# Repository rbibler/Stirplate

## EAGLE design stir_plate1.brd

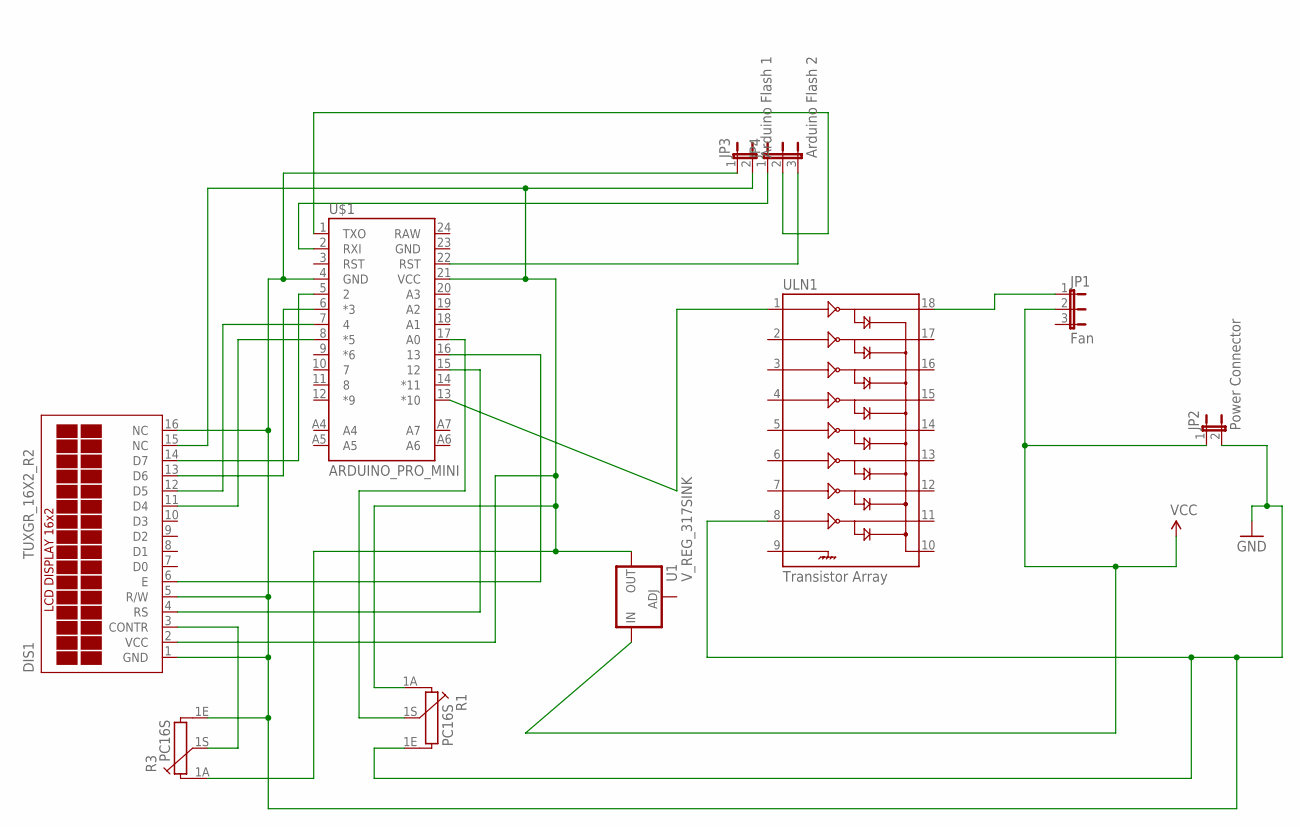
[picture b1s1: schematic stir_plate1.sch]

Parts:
DIS1: TUXGR_16X2_R2
JP1: Fan; JP2
JP2: Power Connector; JP1
JP3: Arduino Flash 1; JP1
JP4: Arduino Flash 2; JP2
R1, R3: PC16S
U1: V_REG_317SINK; TO220-ADJ
U$1: ARDUINO_PRO_MINI
ULN1: Transistor Array; DIL18

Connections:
GND: DIS1.1 (GND), DIS1.5 (R/W), DIS1.16 (NC), JP2.2, JP3.1, R1.1E, R3.1E, U$1.4 (GND), ULN1.8
unnamed: U$1.13 (*10), ULN1.1
unnamed: JP1.1, ULN1.18
unnamed: DIS1.3 (CONTR), R3.1S
unnamed: DIS1.11 (D4), U$1.8 (*5)
unnamed: JP4.1, U$1.2 (RXI)
unnamed: DIS1.12 (D5), U$1.7 (4)
unnamed: DIS1.2 (VCC), DIS1.15 (NC), JP3.2, R1.1A, R3.1A, U1.OUT, U$1.21 (VCC)
unnamed: DIS1.13 (D6), U$1.6 (*3)
unnamed: DIS1.14 (D7), U$1.5 (2)
unnamed: DIS1.4 (RS), U$1.15 (12)
unnamed: R1.1S, U$1.17 (A0)
unnamed: DIS1.6 (E), U$1.16 (13)
unnamed: JP4.2, U$1.1 (TXO)
unnamed: JP4.3, U$1.22 (RST)
VCC: JP1.2, JP2.1, U1.IN

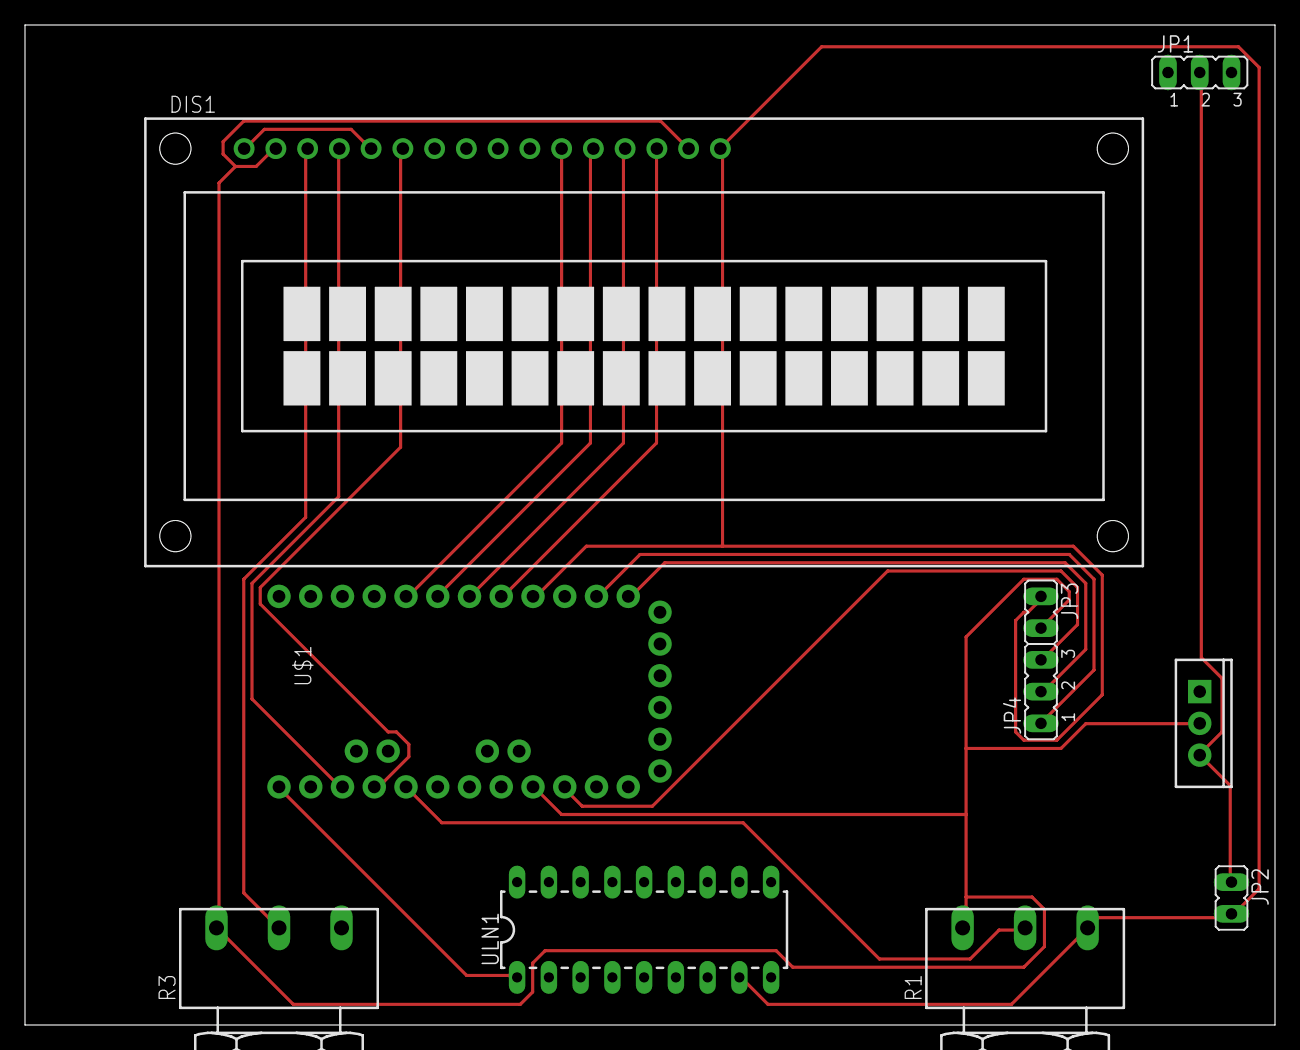
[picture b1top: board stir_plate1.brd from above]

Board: 2 copper layers, 100.0 x 80.0 mm, 10 parts (0 on the bottom side), 16 nets.

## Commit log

2016-10-18 :circus_tent: Added .gitattributes & .gitignore files
2016-10-18 Initial Commit
    This is it.

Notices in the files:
parts and their libraries:
SparkFun-Boards: Licensing: Creative Commons ShareAlike 4.0 International - https://creativecommons.org/licenses/by-sa/4.0
